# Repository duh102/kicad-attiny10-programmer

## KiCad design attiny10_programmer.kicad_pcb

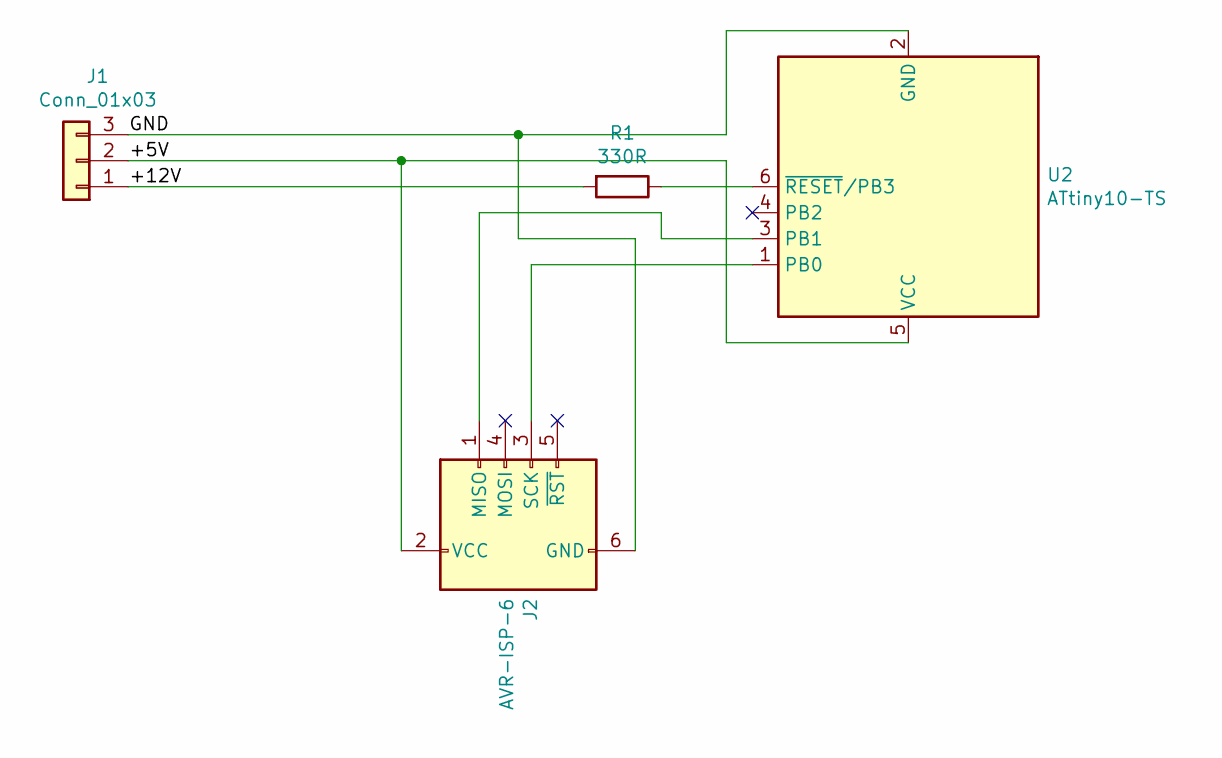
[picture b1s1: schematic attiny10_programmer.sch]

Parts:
J1: Conn_01x03; PinHeader_1x03_P2.54mm_Vertical
J2: AVR-ISP-6; PinHeader_2x03_P2.54mm_Vertical
R1: 330R; R_0805_2012Metric
U2: ATtiny10-TS; PinHeader_2x03_P2.54mm_Vertical

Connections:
/+5V: J1.2, J2.2 (VCC), U2.5 (VCC)
/+12V: J1.1, R1.2
/GND: J1.3, J2.6 (GND), U2.2 (GND)
unnamed: J2.1 (MISO), U2.3 (PB1)
unnamed: J2.3 (SCK), U2.1 (PB0)
unnamed: R1.1, U2.6 (~RESET~/PB3)

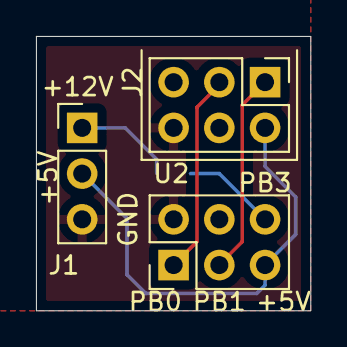
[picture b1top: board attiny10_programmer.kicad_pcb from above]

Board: 2 copper layers, 15.2 x 15.2 mm, 4 parts (1 on the bottom side), 6 nets.

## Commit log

2019-11-18 Add current limiting resistor on +12v
2019-11-18 Add byline
2020-12-09 Fix&Update gitignore
